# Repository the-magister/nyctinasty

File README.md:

# Nyctinasty Oasis

Submitting for an Honoraria grant for Burning Man 2018.  An interactive playground celebrating the rhythm of night and day. By day the piece provides climbing fun, shade, and misters powered by movement. At night the lights come on, the sound enlivens and the fire and smoke show begins. The final night, the flower-like structure will wilt and burn.

## Physical Description

Three climbable outriggers around a 32 ft radius circle surround a central flower. 16 ft tall, the outriggers support 20 people dancing and climbing. Built of wood and covered in shade cloth, they feature water misters and hammocks for daytime refuge. Misters are housed in vines, flowers decorate the structure, and leaf-like streamers unfurl overhead.

The center flower is a 16 ft tall metal structure comprised of three metal petals with flame and fog effect heads. Each petal is 3 ft W x 6ft L * 16 ft H. They each have a secured metal base, topped with a foldable rigid origami paneling crafted from 16 gauge metal with metal hinging. A propane accumulator is stored within each petal and plumbed to the tip of the paneling. Each base has 50 meters of RGB LEDs wrapped around the accumulator, diffused by semi-opaque HDPE panels.

## Interactivity and Mission

Nyctinasty Oasis is a day/night playground. Each outrigger is a climbable shade structure. With chill day music, participants can climb the structure, play with it to coax cooling mists, or take a break in the hammocks underneath.
Also incorporated is a sound puzzle, where the participants use movement to mix together multiple tracks of sounds to complete a song. Each outrigger contains three sensor bars which detect the frequency and location of the participants using infrared sensors. The game incorporates collaborative movement to create a coherent whole. Songs composed of three tracks (e.g., bass/melody/vocals) will have each track randomly assigned. As the dancers move and align their tracks, the lights and music will synchronize, rewarding with cooling mists and sounds during the day, and coordinated light at night.

The central flower coordinates with fire and fog. At the end of the week, Nyctinasty Oasis is burned, leaving participants to wonder if it was all a mirage.

## Philosophy

Nyctinasty is the circadian rhythmic movement of plants in response to day and night. An oasis is a fertile habitat found in a desert. Together, a nyctinasty oasis is a retreat that provides both respite and reactivity that changes and is available from day to night. We seek to express how experience varies depending on time of day, point of view, activity level, and community involvement. Nyctinasty Oasis has diurnal features that return upon sunrise and sundown, as well as constant features. During the day, Nyctinasty Oasis provides solace with shade, hammocks, and water misters. Chill, low-volume ambient music is controlled by interaction with the outrigger sensors. At night, the lights come out to play along with a multi-track interactive musical and fire experience that varies based on the number of participants at points along the outriggers. The Nyctinasty Oasis experience is externally guided by regular circadian elements, but also influenced by user participation and determination. The Nyctinasty Oasis also provides constants, a playground standing ready for climbing, hiding, and chilling day or night. We wish to communicate to participants that the experience will be regular, changeable, and replenishing.

## Hardware 

Nyctinasty functions as a distributed set of microcontrollers (uC).  In this sense, the project shares the archetecture of an IoT system.  However, processing is all conducted locally (as opposed to typical cloud-based IoT processing).

### Devices

* Networking: WiFi router, RFM69H(C)W peer-to-peer, FM for sound.
* Wemos D1 Mini (ESP8266): and mainstay microcontroller (uC).
* Arduino Nano (Atmel 328P): analog-to-digitial conversion
* Moteino R3 (Atmel 328P): bridge to legacy HopeRF-mediated peer-to-peer hardware
* Tsunami Super WAV Trigger (ARM Cortex m7): audio generation
* Sharp IR Distance Sensor (GP2Y0A02YK0F): range and motion detection
* Addressable LEDs (WS2811): lighting
* pump (TBD): mister system

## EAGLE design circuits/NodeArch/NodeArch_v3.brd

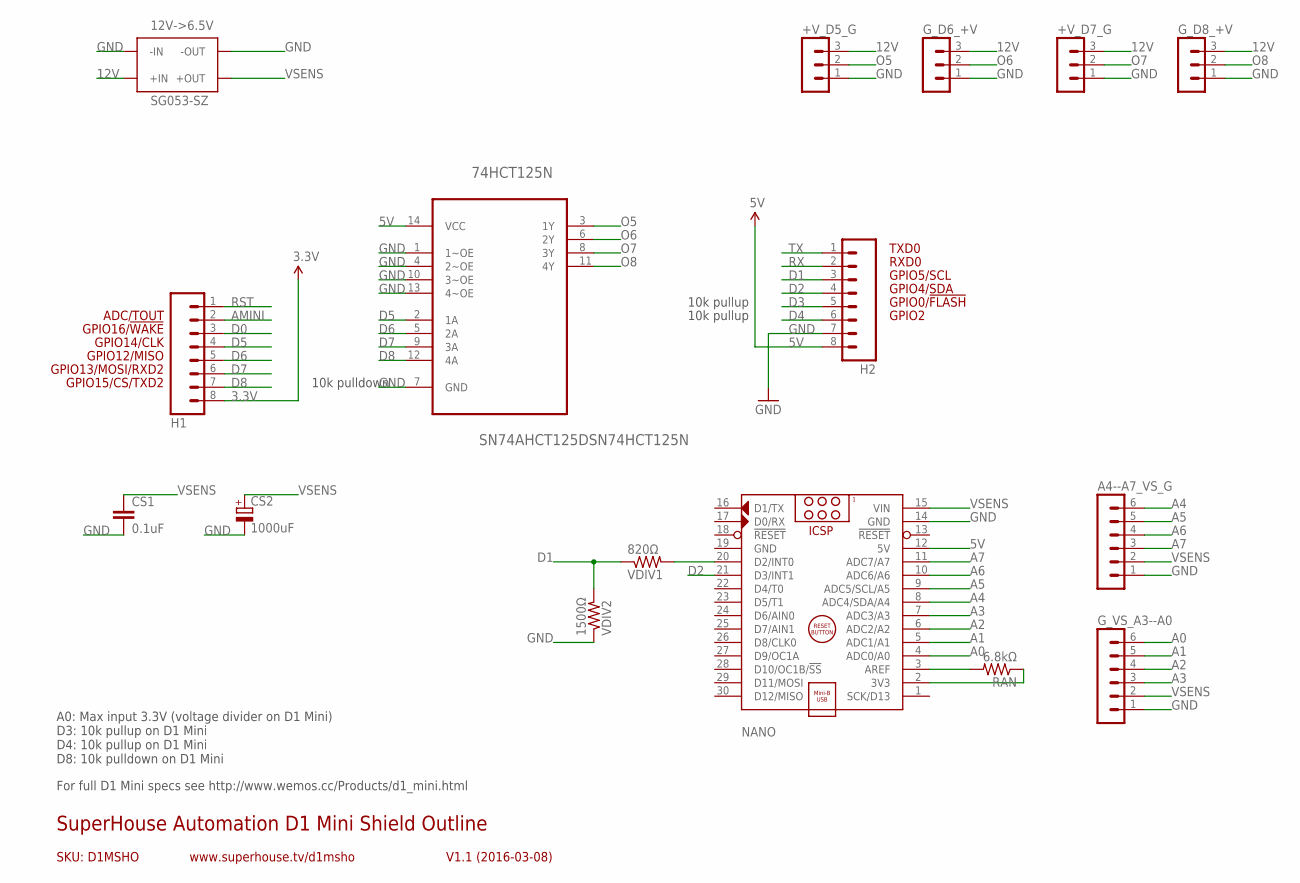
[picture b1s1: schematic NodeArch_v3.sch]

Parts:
12V->6.5V: SG053-SZ
74HCT125N: SN74AHCT125DSN74HCT125N; DIP254P762X508-14
+V_D5_G, +V_D7_G: MA03-1
A4--A7_VS_G: MA06-1
CS1: 0.1uF; C025-025X050
CS2: 1000uF; E5-10,5
G_D6_+V, G_D8_+V: MA03-1
G_VS_A3--A0: MA06-1
H1, H2: M08; 1X08
NANO: ARDUINO_NANO
RAN: 6.8kΩ; 0207/2V
VDIV1: 820Ω; 0207/2V
VDIV2: 1500Ω; 0207/2V

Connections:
3.3V: H1.8
5V: 74HCT125N.14 (VCC), H2.8, NANO.12 (5V)
12V: 12V->6.5V.P$3 (+IN), 12V->6.5V.P$4 (+IN), +V_D5_G.3, +V_D7_G.3, G_D6_+V.3, G_D8_+V.3
A0: G_VS_A3--A0.6, NANO.4 (ADC0/A0)
A1: G_VS_A3--A0.5, NANO.5 (ADC1/A1)
A2: G_VS_A3--A0.4, NANO.6 (ADC2/A2)
A3: G_VS_A3--A0.3, NANO.7 (ADC3/A3)
A4: A4--A7_VS_G.6, NANO.8 (ADC4/SDA/A4)
A5: A4--A7_VS_G.5, NANO.9 (ADC5/SCL/A5)
A6: A4--A7_VS_G.4, NANO.10 (ADC6/A6)
A7: A4--A7_VS_G.3, NANO.11 (ADC7/A7)
AMINI: H1.2
D0: H1.3
D1: H2.3, VDIV1.1, VDIV2.2
D2: H2.4, NANO.21 (D3/INT1)
D3: H2.5
D4: H2.6
D5: 74HCT125N.2 (1A), H1.4
D6: 74HCT125N.5 (2A), H1.5
D7: 74HCT125N.9 (3A), H1.6
D8: 74HCT125N.12 (4A), H1.7
GND: 12V->6.5V.P$1 (-IN), 12V->6.5V.P$2 (-IN), 12V->6.5V.P$7 (-OUT), 12V->6.5V.P$8 (-OUT), 74HCT125N.1 (1~OE), 74HCT125N.4 (2~OE), 74HCT125N.7 (GND), 74HCT125N.10 (3~OE), 74HCT125N.13 (4~OE), +V_D5_G.1, +V_D7_G.1, A4--A7_VS_G.1, CS1.2, CS2.-, G_D6_+V.1, G_D8_+V.1, G_VS_A3--A0.1, H2.7, NANO.14 (GND), NANO.19 (GND), VDIV2.1
unnamed: NANO.3 (AREF), RAN.2
unnamed: NANO.2 (3V3), RAN.1
unnamed: NANO.20 (D2/INT0), VDIV1.2
O5: 74HCT125N.3 (1Y), +V_D5_G.2
O6: 74HCT125N.6 (2Y), G_D6_+V.2
O7: 74HCT125N.8 (3Y), +V_D7_G.2
O8: 74HCT125N.11 (4Y), G_D8_+V.2
RST: H1.1
RX: H2.2
TX: H2.1
VSENS: 12V->6.5V.P$5 (+OUT), 12V->6.5V.P$6 (+OUT), A4--A7_VS_G.2, CS1.1, CS2.+, G_VS_A3--A0.2, NANO.15 (VIN)

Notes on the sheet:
GPIO2
GPIO0/!FLASH
GPIO12/MISO
GPIO4/SDA
GPIO5/SCL
RXD0
TXD0
GPIO13/MOSI/RXD2
GPIO14/CLK
GPIO15/CS/TXD2
GPIO16/!WAKE
SKU: D1MSHO
SuperHouse Automation D1 Mini Shield Outline
V1.1 (2016-03-08)
www.superhouse.tv/d1msho
ADC/TOUT
A0: Max input 3.3V (voltage divider on D1 Mini) D3: 10k pullup on D1 Mini D4: 10k pullup on D1 Mini D8: 10k pulldown on D1 Mini
10k pulldown
10k pullup
For full D1 Mini specs see http://www.wemos.cc/Products/d1_mini.html

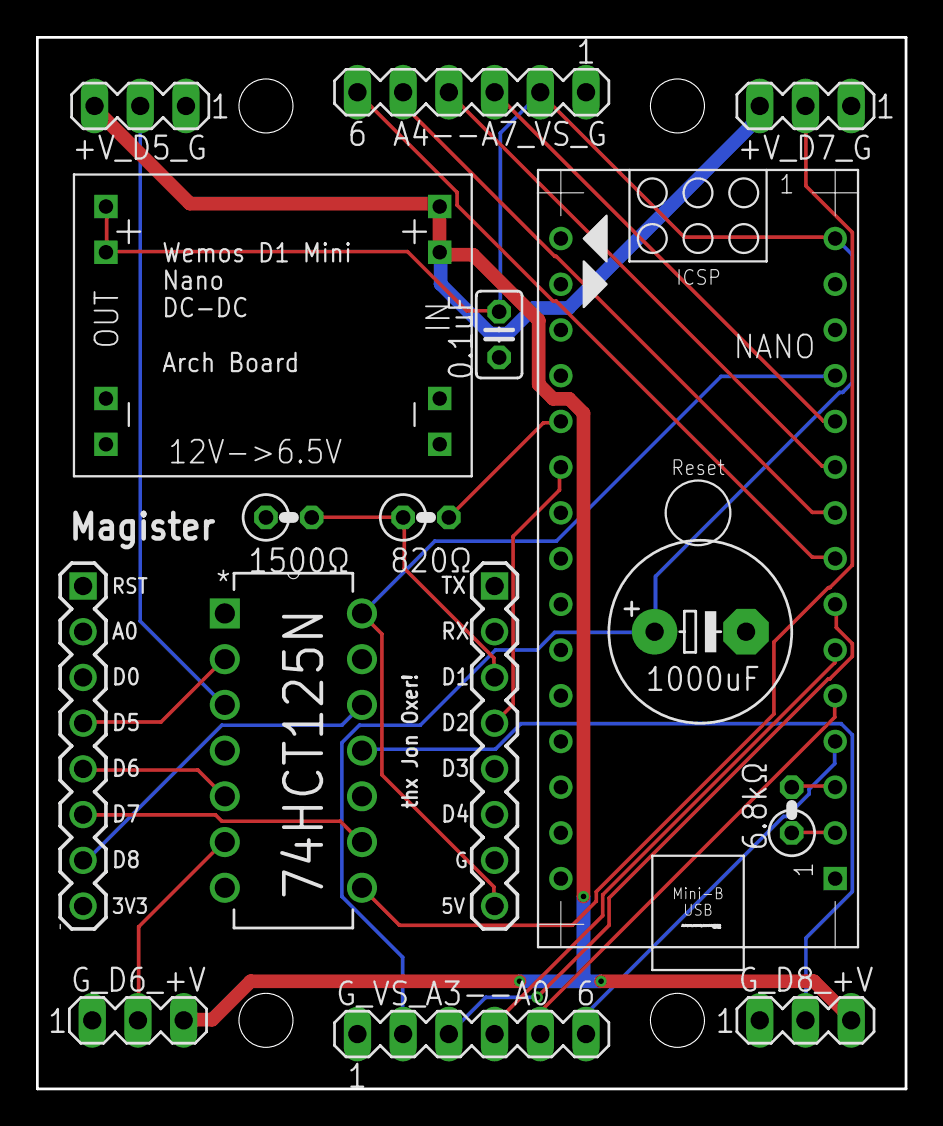
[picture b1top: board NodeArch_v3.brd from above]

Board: 2 copper layers, 48.3 x 58.4 mm, 16 parts (0 on the bottom side), 25 nets.

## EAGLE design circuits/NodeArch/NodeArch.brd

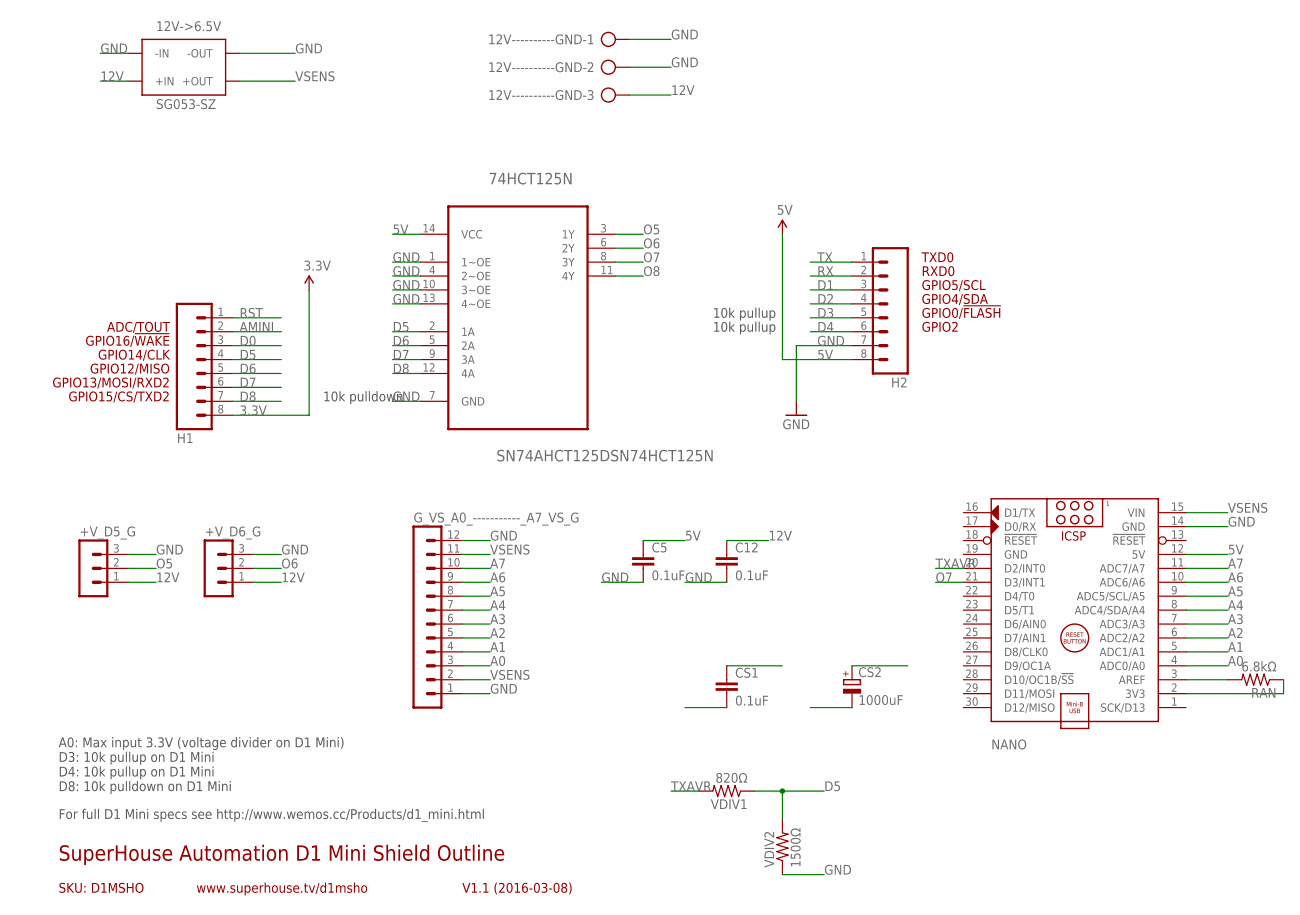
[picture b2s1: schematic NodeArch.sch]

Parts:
12V----------GND: AK500/3
12V->6.5V: SG053-SZ
74HCT125N: SN74AHCT125DSN74HCT125N; DIP254P762X508-14
+V_D5_G, +V_D6_G: MA03-1
C5, C12: 0.1uF; C025-025X050
CS1: 0.1uF; C025-025X050
CS2: 1000uF; E5-10,5
G_VS_A0_-----------_A7_VS_G: MA12-1
H1, H2: M08; 1X08
NANO: ARDUINO_NANO
RAN: 6.8kΩ; 0207/2V
VDIV1: 820Ω; 0207/2V
VDIV2: 1500Ω; 0207/2V

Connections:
3.3V: H1.8
5V: 74HCT125N.14 (VCC), C5.1, H2.8, NANO.12 (5V)
12V: 12V----------GND.3, 12V->6.5V.P$3 (+IN), 12V->6.5V.P$4 (+IN), +V_D5_G.1, +V_D6_G.1, C12.1
A0: G_VS_A0_-----------_A7_VS_G.3, NANO.4 (ADC0/A0)
A1: G_VS_A0_-----------_A7_VS_G.4, NANO.5 (ADC1/A1)
A2: G_VS_A0_-----------_A7_VS_G.5, NANO.6 (ADC2/A2)
A3: G_VS_A0_-----------_A7_VS_G.6, NANO.7 (ADC3/A3)
A4: G_VS_A0_-----------_A7_VS_G.7, NANO.8 (ADC4/SDA/A4)
A5: G_VS_A0_-----------_A7_VS_G.8, NANO.9 (ADC5/SCL/A5)
A6: G_VS_A0_-----------_A7_VS_G.9, NANO.10 (ADC6/A6)
A7: G_VS_A0_-----------_A7_VS_G.10, NANO.11 (ADC7/A7)
AMINI: H1.2
D0: H1.3
D1: H2.3
D2: H2.4
D3: H2.5
D4: H2.6
D5: 74HCT125N.2 (1A), H1.4, VDIV1.1, VDIV2.2
D6: 74HCT125N.5 (2A), H1.5
D7: 74HCT125N.9 (3A), H1.6
D8: 74HCT125N.12 (4A), H1.7
GND: 12V----------GND.1, 12V----------GND.2, 12V->6.5V.P$1 (-IN), 12V->6.5V.P$2 (-IN), 12V->6.5V.P$7 (-OUT), 12V->6.5V.P$8 (-OUT), 74HCT125N.1 (1~OE), 74HCT125N.4 (2~OE), 74HCT125N.7 (GND), 74HCT125N.10 (3~OE), 74HCT125N.13 (4~OE), +V_D5_G.3, +V_D6_G.3, C5.2, C12.2, CS1.2, CS2.-, G_VS_A0_-----------_A7_VS_G.1, G_VS_A0_-----------_A7_VS_G.12, H2.7, NANO.14 (GND), NANO.19 (GND), VDIV2.1
unnamed: NANO.3 (AREF), RAN.2
unnamed: NANO.2 (3V3), RAN.1
O5: 74HCT125N.3 (1Y), +V_D5_G.2
O6: 74HCT125N.6 (2Y), +V_D6_G.2
O7: 74HCT125N.8 (3Y), NANO.21 (D3/INT1)
O8: 74HCT125N.11 (4Y)
RST: H1.1
RX: H2.2
TX: H2.1
TXAVR: NANO.20 (D2/INT0), VDIV1.2
VSENS: 12V->6.5V.P$5 (+OUT), 12V->6.5V.P$6 (+OUT), CS1.1, CS2.+, G_VS_A0_-----------_A7_VS_G.2, G_VS_A0_-----------_A7_VS_G.11, NANO.15 (VIN)

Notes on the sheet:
GPIO2
GPIO0/!FLASH
GPIO12/MISO
GPIO4/SDA
GPIO5/SCL
RXD0
TXD0
GPIO13/MOSI/RXD2
GPIO14/CLK
GPIO15/CS/TXD2
GPIO16/!WAKE
SKU: D1MSHO
SuperHouse Automation D1 Mini Shield Outline
V1.1 (2016-03-08)
www.superhouse.tv/d1msho
ADC/TOUT
A0: Max input 3.3V (voltage divider on D1 Mini) D3: 10k pullup on D1 Mini D4: 10k pullup on D1 Mini D8: 10k pulldown on D1 Mini
10k pulldown
10k pullup
For full D1 Mini specs see http://www.wemos.cc/Products/d1_mini.html

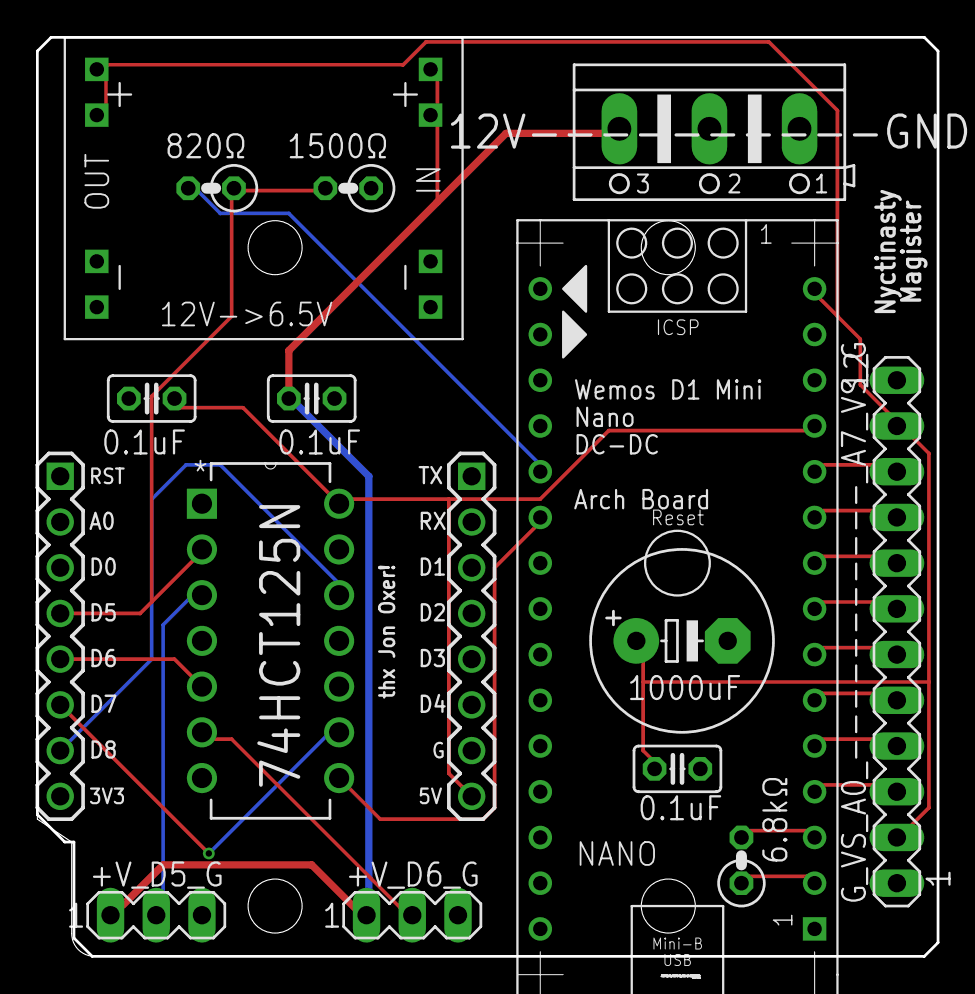
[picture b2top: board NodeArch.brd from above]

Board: 2 copper layers, 50.0 x 51.1 mm, 16 parts (0 on the bottom side), 22 nets.

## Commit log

2017-08-14 pushed a start
2017-08-15 added MQTT protocols
2017-08-24 Added datasheet
2017-08-24 stubbed out Sensor, Light, MIDI
2017-08-24 touch-up to Sensor and Light
2017-08-25 Added in tests
2017-08-25 moar datasheets
2017-08-25 have MQTT enabled router
2017-08-26 src/Sensor should spew MQTT values
2017-08-26 checkpoint before moving to mqtt class
2017-08-26 Light moved to Comms framework
2017-08-27 prototype up
2017-08-28 Added sensor viz. Requires processing 3+
2017-08-28 comments on SensorViz.pde
2017-09-03 added datasheets and library for 850nm IR sensors
2017-09-04 added skeinSensor1, using the Sharp IR rangers
2017-09-04 Labor Day labor
2017-09-10 Fixed reset pin. Reduced max network packet to 64 bytes to spend transmital
2017-09-17 moved to 12bit ADC by oversampling on the Nano
2017-09-26 Basic midi prototype done
2017-09-26 Don't initialize broken sensor
2017-09-26 Sharp IR sensors added
2017-09-30 Sharp IR set up
2017-10-01 Sharp IR has proper range calculation
2017-10-05 Added multiple sensor support
2017-10-30 moved to struct messages
2017-11-02 Fix sending of messages using struct length not pointer
2017-11-02 fuck git
2017-11-02 tinkered with ADC device
2017-11-05 experimental change to lighting to linearize distance to perception
2017-11-09 sharp sensors working
2017-11-12 light up
2017-11-12 ADC is working well
2017-11-16 new hardware build
2017-11-19 updated test rig
2017-11-19 new hardward working
2017-11-20 added first pass at FFT for gesture recognition
2017-12-08 should have a working system
2017-12-08 refactored to template pubsub
2017-12-09 rename to Sepal
2017-12-12 dammit esp32 and your not working adc2
2017-12-18 working comms
2017-12-20 working fft
2017-12-28 first push prototype
2017-12-29 documented WiFi-RFM bridge pinout
2017-12-29 refactored comms
2018-01-01 refactored comms to a class. tidier.
2018-01-01 added a processing sketch
2018-01-02 processing script added.
2018-01-04 processing 3D looks good
2018-01-04 refined 3d model
2018-01-05 added lighting and sensor animations
2018-01-05 Added mouse navigation
2018-01-05 Added viewpoints
2018-01-05 Reduce sphere triangles to keep framerate high during simulation
2018-01-06 Removed generated application
2018-01-10 added Qt movie maker
2018-01-11 Added new center piece. Updated cameras
2018-01-13 Added steps
2018-01-19 processing sketchs and a variety of stand-alone modules added
2018-01-19 palette code added
2018-01-21 colorpallete rig complete
2018-01-22 OTA example
2018-01-25 Removed files. Added stairs
2018-01-29 pumps added. weighted correlation added
2018-03-09 start of MTD modeling
2018-04-20 test
2018-04-20 Arch board v3
2018-05-14 production boards look good
2018-05-19 Sepal_Arch and _Distance working reasonably well
2018-05-20 moved over to a single sepal in codebase
2018-05-26 10 Hz distance data too
2018-05-29 stubbed out Sepal_Sound for Danne
2018-05-31 Sepal_Sound hardware up
2018-06-01 Adjusted for six sensors
2018-06-02 June 2nd hardware complete
2018-06-02 saturday update
2018-06-08 Pumps stubbed
2018-06-11 Stubbed out Water Works more fully
2018-06-12 WaterWorks up
2018-06-12 effed up Arch code somehow
2018-06-14 made the offline pump shutdown stupider
2018-06-15 moar WaterWorks
2018-06-20 Coordinator dumping data
2018-06-20 new systemStates
2018-06-20 renamed stuff in src to align with actuality
2018-06-21 correlation might work
2018-06-24 water works up
2018-06-26 Coordinator built out with game states
2018-06-28 Coordinator sorta works
2018-06-28 untested, but Arch should have better animations now
2018-06-29 thursday
2018-06-29 Added sounds
2018-06-29 New sounds
2018-06-29 Updated sound to latest states
2018-07-01 trigger working
2018-07-01 WaterWorks ready to ship
2018-07-02 new coordination data; moving to magister branch to test
2018-07-04 Tuesday
2018-07-04 Added id to states. Added pos/neg changes to sound. Added gunfire, not tested
2018-07-04 Removed converted files. Added source files
2018-07-04 Wednesday
2018-07-07 Friday
2018-07-07 Saturday; packed for CNW18
2018-07-08 Added more sounds
2018-07-08 Sunday morning
2018-07-09 Sunday
2018-07-09 Monday
2018-07-10 Tuesday, back in the world
2018-07-11 Wednesday morning
2018-07-16 post cnw18; awesome

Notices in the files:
parts and their libraries:
freetronics-original: Licensing: CC v3.0 Share-Alike You are welcome to use this library for commercial purposes.
